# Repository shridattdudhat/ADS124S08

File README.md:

# ADS124S08

## 24-bit, 4-kSPS, 12-ch delta-sigma ADC with PGA and voltage reference for sensor measurement

24bit ADC | SPI

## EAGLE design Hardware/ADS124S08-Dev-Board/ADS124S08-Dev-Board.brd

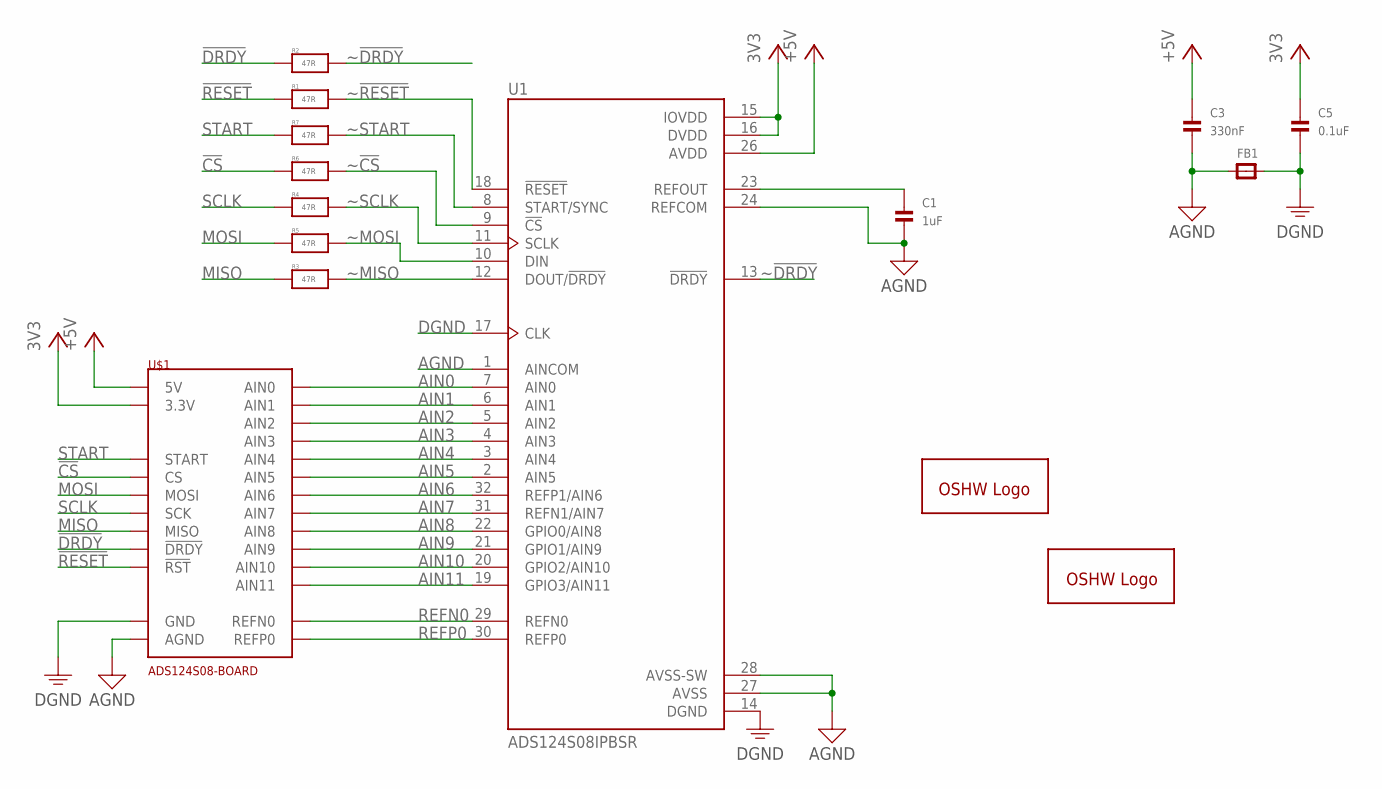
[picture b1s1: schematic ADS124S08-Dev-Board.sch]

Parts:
C1: 1uF; C0603-MINI; MPN 08055C104JAT2A
C3: 330nF; C0603-MINI; MPN 08055C104JAT2A
C5: 0.1uF; C0603-MINI; MPN 08055C104JAT2A
FB1: FERRITE_0603; _0603
GOLD_ORB_SM1: OSHWLOGOLOGO5MM; OSHW_5MM
GOLD_ORB_SM2: OSHWLOGOLOGO8MM; OSHW_8MM
R1, R2, R3, R4, R5, R6, R7: 47R; R0603-MINI
U1: ADS124S08IPBSR; QFP50P700X700X120-32N
U$1: ADS124S08-BOARD

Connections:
3V3: C5.1, U1.15 (IOVDD), U1.16 (DVDD), U$1.15 (3.3V)
!CS: R6.1, U$1.21 (CS)
!DRDY: R2.1, U$1.17 (!DRDY)
!RESET: R1.1, U$1.16 (!RST)
+5V: C3.1, U1.26 (AVDD), U$1.14 (5V)
AGND: C1.2, C3.2, FB1.1, U1.1 (AINCOM), U1.24 (REFCOM), U1.27 (AVSS), U1.28 (AVSS-SW), U$1.25 (AGND)
AIN0: U1.7 (AIN0), U$1.12 (AIN0)
AIN1: U1.6 (AIN1), U$1.11 (AIN1)
AIN2: U1.5 (AIN2), U$1.10 (AIN2)
AIN3: U1.4 (AIN3), U$1.9 (AIN3)
AIN4: U1.3 (AIN4), U$1.8 (AIN4)
AIN5: U1.2 (AIN5), U$1.7 (AIN5)
AIN6: U1.32 (REFP1/AIN6), U$1.6 (AIN6)
AIN7: U1.31 (REFN1/AIN7), U$1.5 (AIN7)
AIN8: U1.22 (GPIO0/AIN8), U$1.4 (AIN8)
AIN9: U1.21 (GPIO1/AIN9), U$1.3 (AIN9)
AIN10: U1.20 (GPIO2/AIN10), U$1.2 (AIN10)
AIN11: U1.19 (GPIO3/AIN11), U$1.1 (AIN11)
DGND: C5.2, FB1.2, U1.14 (DGND), U1.17 (CLK), U$1.13 (GND), U$1.26 (GND)
MISO: R3.1, U$1.18 (MISO)
MOSI: R5.1, U$1.20 (MOSI)
unnamed: C1.1, U1.23 (REFOUT)
REFN0: U1.29 (REFN0), U$1.23 (REFN0)
REFP0: U1.30 (REFP0), U$1.24 (REFP0)
SCLK: R4.1, U$1.19 (SCK)
START: R7.1, U$1.22 (START)
~!CS: R6.2, U1.9 (!CS)
~!DRDY: R2.2, U1.13 (!DRDY)
~!RESET: R1.2, U1.18 (!RESET)
~MISO: R3.2, U1.12 (DOUT/!DRDY)
~MOSI: R5.2, U1.10 (DIN)
~SCLK: R4.2, U1.11 (SCLK)
~START: R7.2, U1.8 (START/SYNC)

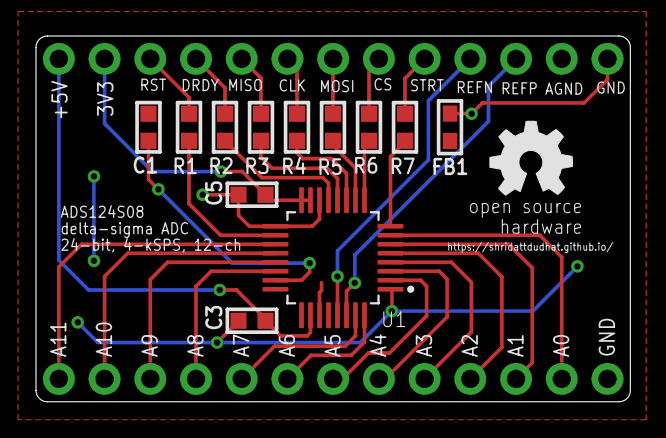
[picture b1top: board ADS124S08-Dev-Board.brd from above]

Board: 2 copper layers, 33.0 x 20.3 mm, 15 parts (1 on the bottom side), 33 nets.

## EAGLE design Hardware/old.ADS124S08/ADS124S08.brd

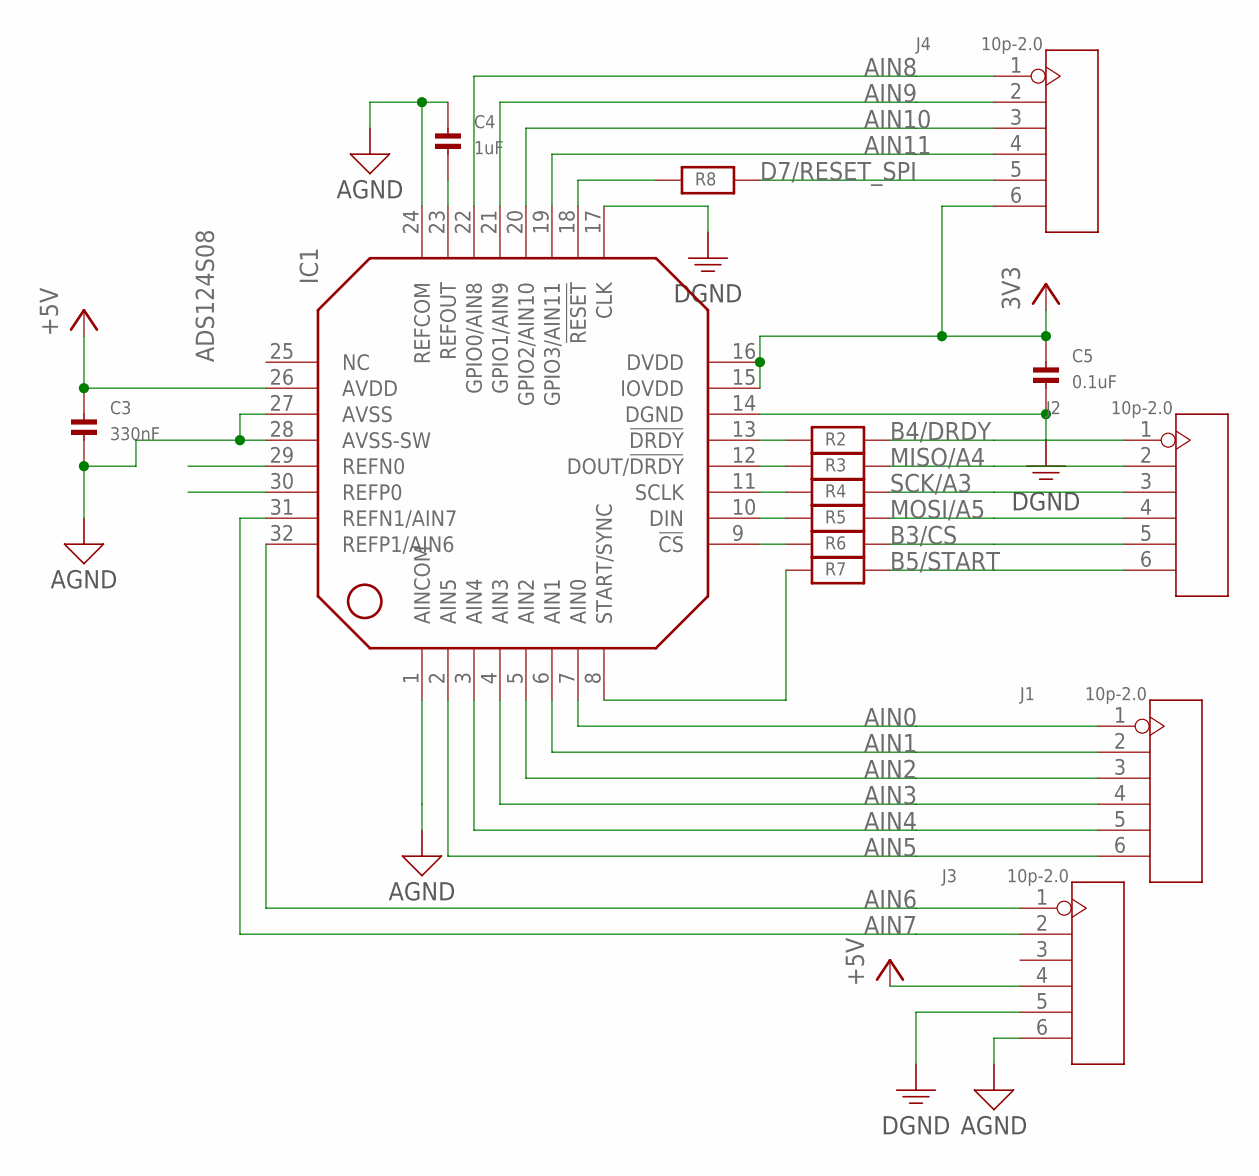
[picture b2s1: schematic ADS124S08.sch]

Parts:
C3: 330nF; 0805; MPN 08055C104JAT2A
C4: 1uF; 0805; MPN 08055C104JAT2A
C5: 0.1uF; 0805; MPN 08055C104JAT2A
IC1: ADS124S08
J1, J2, J3, J4: 10p-2.0; H10-2.0
R2, R3, R4, R5, R7, R8: 47; 0603
R6: RESISTOR0603; 0603

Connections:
3V3: C5.1, IC1.15 (IOVDD), IC1.16 (DVDD), J4.6
!RESET: IC1.18 (!RESET), R8.1
+5V: C3.1, IC1.26 (AVDD), J3.4
AGND: C3.2, C4.1, IC1.1 (AINCOM), IC1.24 (REFCOM), IC1.27 (AVSS), IC1.28 (AVSS-SW), J3.6
AIN0: IC1.7 (AIN0), J1.1
AIN1: IC1.6 (AIN1), J1.2
AIN2: IC1.5 (AIN2), J1.3
AIN3: IC1.4 (AIN3), J1.4
AIN4: IC1.3 (AIN4), J1.5
AIN5: IC1.2 (AIN5), J1.6
AIN6: IC1.32 (REFP1/AIN6), J3.1
AIN7: IC1.31 (REFN1/AIN7), J3.2
AIN8: IC1.22 (GPIO0/AIN8), J4.1
AIN9: IC1.21 (GPIO1/AIN9), J4.2
AIN10: IC1.20 (GPIO2/AIN10), J4.3
AIN11: IC1.19 (GPIO3/AIN11), J4.4
B3/CS: J2.5, R6.2
B4/DRDY: J2.1, R2.2
B5/START: J2.6, R7.2
CS: IC1.9 (!CS), R6.1
D7/RESET_SPI: J4.5, R8.2
DGND: C5.2, IC1.14 (DGND), IC1.17 (CLK), J3.5
DRDY: IC1.13 (!DRDY), R2.1
MISO: IC1.12 (DOUT/!DRDY), R3.1
MISO/A4: J2.2, R3.2
MOSI: IC1.10 (DIN), R5.1
MOSI/A5: J2.4, R5.2
REFOUT: C4.2, IC1.23 (REFOUT)
SCK: IC1.11 (SCLK), R4.1
SCK/A3: J2.3, R4.2
START: IC1.8 (START/SYNC), R7.1

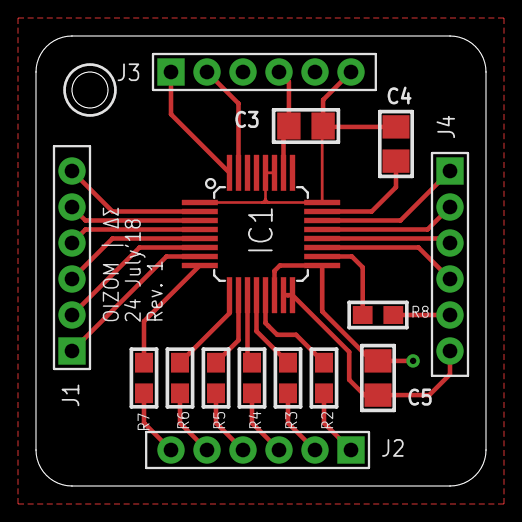
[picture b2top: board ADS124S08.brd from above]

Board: 2 copper layers, 25.0 x 25.0 mm, 15 parts (0 on the bottom side), 31 nets.

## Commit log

2018-07-24 SCH | PCB
2018-07-24 Hardware
2020-09-15 Set theme jekyll-theme-cayman
2020-09-16 new updates | Creation of new Dev Module for ADS124S08 IC
2020-09-16 new Board SCH
2020-09-16 Component placement done
2020-09-16 unwanted file detele
2020-09-22 GERBER GENERATION
2020-10-13 Set theme jekyll-theme-hacker
2021-07-19 Create LICENSE
2021-07-28 Arduino Example

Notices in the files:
parts and their libraries:
microbuilder: This work is placed in the public domain, and may be freely used for commercial and non-commercial work with the following conditions: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
